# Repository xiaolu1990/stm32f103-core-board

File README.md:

## What is this?

This is a customized development board for STM32F103C8T6 Microcontroller. It can be powered and communicated to PC using the USB-C cable in USB 2.0 highspeed. The small size also allows to fit nicely either on a breadboard or as a module on your pcb.

## How to open the project?

Use Kicad 9.0+ versions to open the project.

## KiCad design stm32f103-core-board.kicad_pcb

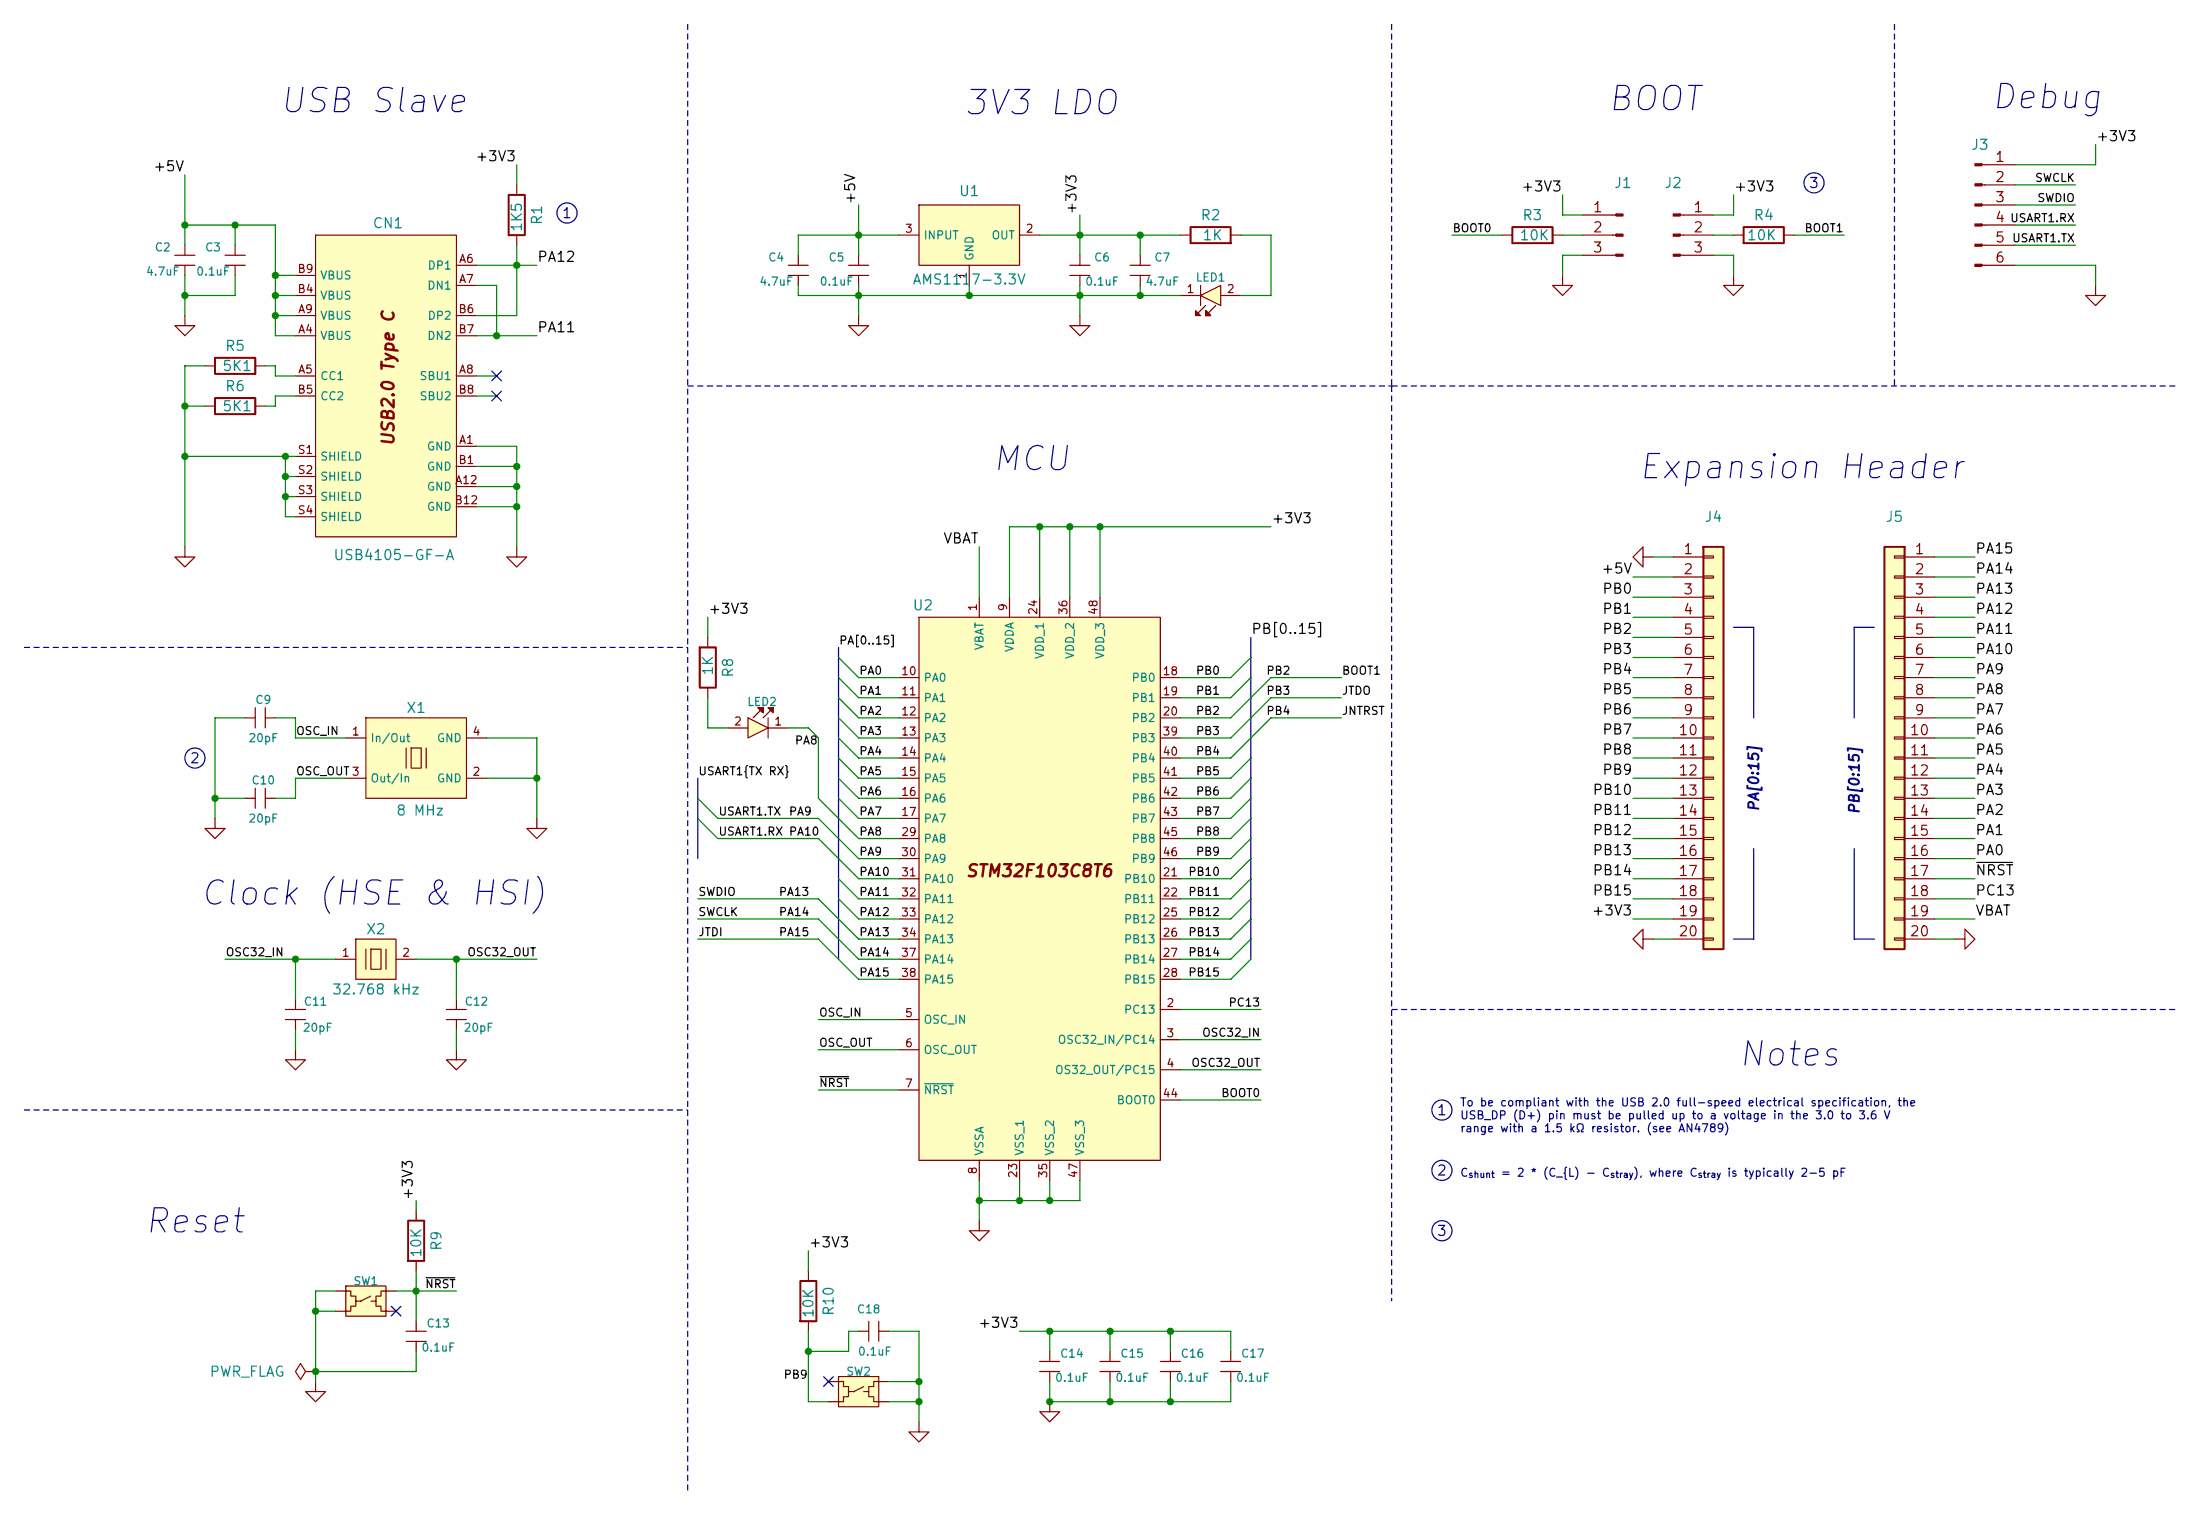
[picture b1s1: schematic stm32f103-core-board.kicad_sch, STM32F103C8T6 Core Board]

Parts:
C2, C4, C7: 4.7uF; C_SMD_0603; MPN GRM188R61E475KE11D
C3, C5, C6, C13, C14, C15, C16, C17, C18: 0.1uF; C_SMD_0402; MPN GRM155R71C104KA88J
C9, C10, C11, C12: 20pF; C_SMD_0402; MPN GRM1555C1H200JA01D
CN1: USB4105-GF-A; MPN USB4105-GF-A
J1, J2: Conn_01x03_Pin; PinHeader_1x03_P2.54mm_Vertical
J3: SWD; Castellated_PinHeader_1x6_2.54mm
J4, J5: Conn_01x20; Castellated_PinHeader_1x20_2.54mm
LED1: 150060VS75000; LED_SMD_0603; MPN 150060VS75000
LED2: 150060YS75000; LED_SMD_0603; MPN 150060YS75000
R1: 1K5; R_SMD_0402; MPN RC0402JR-071K5L
R2, R8: 1K; R_SMD_0402; MPN RC0402JR-071KL
R3, R4, R9, R10: 10K; R_SMD_0402; MPN RC0402JR-0710KL
R5, R6: 5K1; R_SMD_0402; MPN RC0402FR-075K1L
SW1, SW2: PTS810; SW_PTS810; MPN PTS810SJM250SMTR LFS
U1: AMS1117-3.3V; MPN AMS1117-3.3V
U2: STM32F103C8T6; MPN STM32F103C8T6
X1: 8 MHz; ECX-32; MPN ECS-80-12-33-JGN-TR
X2: 32.768 kHz; ECX-31B; MPN ECS-.327-12.5-34B-TR

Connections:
/+3V3: C6.2, C7.2, C14.2, C15.2, C16.2, C17.2, J1.1, J2.1, J3.1, J4.19, R1.1, R2.1, R8.2, R9.1, R10.1, U1.2 (OUT), U2.9 (VDDA), U2.24 (VDD_1), U2.36 (VDD_2), U2.48 (VDD_3)
/+5V: C2.2, C3.2, C4.2, C5.2, CN1.A4 (VBUS), CN1.A9 (VBUS), CN1.B4 (VBUS), CN1.B9 (VBUS), J4.2, U1.3 (INPUT)
/BOOT0: R3.1, U2.44 (BOOT0)
/OSC32_IN: C11.2, U2.3 (OSC32_IN/PC14), X2.1 (In/Out)
/OSC32_OUT: C12.2, U2.4 (OS32_OUT/PC15), X2.2 (Out/In)
/OSC_IN: C9.2, U2.5 (OSC_IN), X1.1 (In/Out)
/OSC_OUT: C10.2, U2.6 (OSC_OUT), X1.3 (Out/In)
/PA0: J5.16, U2.10 (PA0)
/PA1: J5.15, U2.11 (PA1)
/PA2: J5.14, U2.12 (PA2)
/PA3: J5.13, U2.13 (PA3)
/PA4: J5.12, U2.14 (PA4)
/PA5: J5.11, U2.15 (PA5)
/PA6: J5.10, U2.16 (PA6)
/PA7: J5.9, U2.17 (PA7)
/PA8: J5.8, LED2.1 (K), U2.29 (PA8)
/PA11: CN1.A7 (DN1), CN1.B7 (DN2), J5.5, U2.32 (PA11)
/PA12: CN1.A6 (DP1), CN1.B6 (DP2), J5.4, R1.2, U2.33 (PA12)
/PA13: J3.3, J5.3, U2.34 (PA13)
/PA14: J3.2, J5.2, U2.37 (PA14)
/PA15: J5.1, U2.38 (PA15)
/PB0: J4.3, U2.18 (PB0)
/PB1: J4.4, U2.19 (PB1)
/PB2: J4.5, R4.1, U2.20 (PB2)
/PB3: J4.6, U2.39 (PB3)
/PB4: J4.7, U2.40 (PB4)
/PB5: J4.8, U2.41 (PB5)
/PB6: J4.9, U2.42 (PB6)
/PB7: J4.10, U2.43 (PB7)
/PB8: J4.11, U2.45 (PB8)
/PB9: C18.2, J4.12, R10.2, SW2.2, U2.46 (PB9)
/PB10: J4.13, U2.21 (PB10)
/PB11: J4.14, U2.22 (PB11)
/PB12: J4.15, U2.25 (PB12)
/PB13: J4.16, U2.26 (PB13)
/PB14: J4.17, U2.27 (PB14)
/PB15: J4.18, U2.28 (PB15)
/PC13: J5.18, U2.2 (PC13)
/USART1.RX: J3.4, J5.6, U2.31 (PA10)
/USART1.TX: J3.5, J5.7, U2.30 (PA9)
/VBAT: J5.19, U2.1 (VBAT)
/~NRST: C13.2, J5.17, R9.2, SW1.4, U2.7 (~NRST)
GND: C2.1, C3.1, C4.1, C5.1, C6.1, C7.1, C9.1, C10.1, C11.1, C12.1, C13.1, C14.1, C15.1, C16.1, C17.1, C18.1, CN1.A1 (GND), CN1.A12 (GND), CN1.B1 (GND), CN1.B12 (GND), CN1.S1 (SHIELD), CN1.S2 (SHIELD), CN1.S3 (SHIELD), CN1.S4 (SHIELD), J1.3, J2.3, J3.6, J4.1, J4.20, J5.20, LED1.1 (K), R5.1, R6.1, SW1.1, SW1.2, SW2.3, SW2.4, U1.1 (GND), U2.8 (VSSA), U2.23 (VSS_1), U2.35 (VSS_2), U2.47 (VSS_3), X1.2 (GND), X1.4 (GND)
unnamed: CN1.A5 (CC1), R5.2
unnamed: CN1.B5 (CC2), R6.2
unnamed: J1.2, R3.2
unnamed: J2.2, R4.2
unnamed: LED1.2 (A), R2.2
unnamed: LED2.2 (A), R8.1

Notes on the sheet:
PA[0:15]
Notes
USB Slave
3V3 LDO
Debug
Expansion Header
MCU
BOOT
Reset
Clock (HSE & HSI)
PB[0:15]
C_{shunt} = 2 * (C_{L) - C_{stray}), where C_{stray} is typically 2-5 pF
To be compliant with the USB 2.0 full-speed electrical specification, the USB_DP (D+) pin must be pulled up to a voltage in the 3.0 to 3.6 V range with a 1.5 kΩ resistor. (see AN4789)

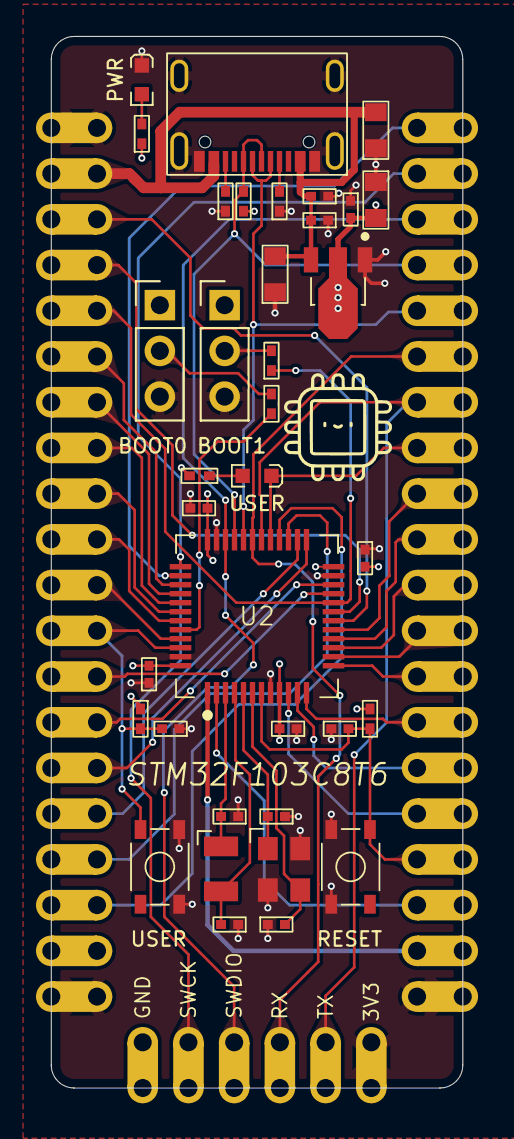
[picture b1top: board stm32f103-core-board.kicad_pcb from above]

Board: 4 copper layers, 22.9 x 58.4 mm, 39 parts (0 on the bottom side), 49 nets.

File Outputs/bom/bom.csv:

"Reference","Qty","Value","MPN","Manufacturer","Description"
"C2,C4,C7","3","4.7uF","GRM188R61E475KE11D","Murata Electronics","CAP CER 4.7UF 25V X5R 0603"
"C3,C5,C6,C13,C14,C15,C16,C17,C18","9","0.1uF","GRM155R71C104KA88J","Murata Electronics","CAP CER 0.1UF 16V X7R 0402"
"C9,C10,C11,C12","4","20pF","GRM1555C1H200JA01D","Murata Electronics","CAP CER 20PF 50V C0G/NP0 0402"
"CN1","1","USB4105-GF-A","USB4105-GF-A","GCT","USB2.0 TYP C"
"J1,J2","2","Conn_01x03_Pin","","","Generic connector, single row, 01x03, script generated"
"J3","1","SWD","","","Generic connector, single row, 01x06, script generated"
"J4,J5","2","Conn_01x20","","","Generic connector, single row, 01x20, script generated (kicad-library-utils/schlib/autogen/connector/)"
"LED1","1","150060VS75000","150060VS75000","Würth Elektronik","LED GREEN CLEAR 0603 SMD"
"LED2","1","150060YS75000","150060YS75000","Würth Elektronik","LED YELLOW CLEAR 0603 SMD"
"R1","1","1K5","RC0402JR-071K5L","YAGEO","RES 1.5K OHM 5% 1/16W 0402"
"R2,R8","2","1K","RC0402JR-071KL","YAGEO","RES 1K OHM 5% 1/16W 0402"
"R3,R4,R9,R10","4","10K","RC0402JR-0710KL","YAGEO","RES 10K OHM 5% 1/16W 0402"
"R5,R6","2","5K1","RC0402FR-075K1L","YAGEO","RES 5.1K OHM 1% 1/16W 0402"
"SW1,SW2","2","PTS810","PTS810SJM250SMTR LFS","C&K","SWITCH TACTILE SPST 4 PIN"
"U1","1","AMS1117-3.3V","AMS1117-3.3V","MSKSEMI","IC REG LIN 3.3V 1A SOT-89"
"U2","1","STM32F103C8T6","STM32F103C8T6","STMicroelectronics","ARM® Cortex®-M3 STM32F1 Microcontroller IC 32-Bit Single-Core 72MHz 64KB (64K x 8) FLASH"
"X1","1","8 MHz","ECS-80-12-33-JGN-TR","ECS","CRYSTAL 8.0000MHZ 12PF SMD"
"X2","1","32.768 kHz","ECS-.327-12.5-34B-TR","ECS","CRYSTAL 32.7680KHZ 12.5PF SMD"

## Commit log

2025-07-14 add README.md
